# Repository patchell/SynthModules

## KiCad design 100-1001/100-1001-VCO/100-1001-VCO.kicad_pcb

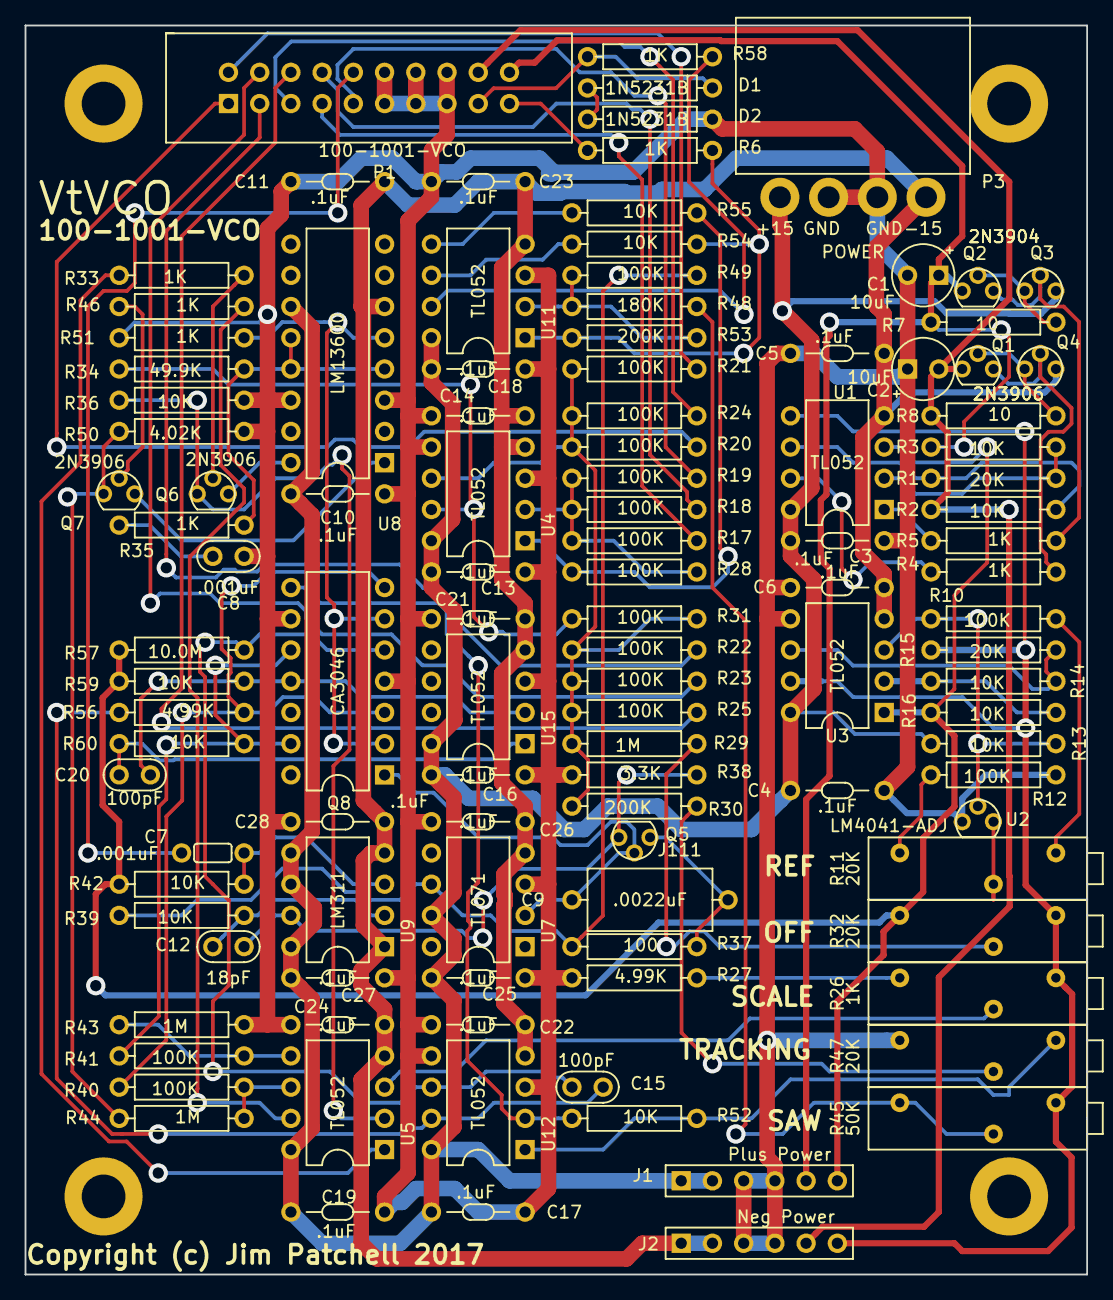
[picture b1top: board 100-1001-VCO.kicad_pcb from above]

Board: 2 copper layers, 86.4 x 101.6 mm, 116 parts (0 on the bottom side), 75 nets.

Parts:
C1, C2: 10uF; Cap-Pol-Rad-0.2_0.1
C3, C4, C5, C6, C10, C11, C13, C14, C16, C17, C18, C19, C21, C22, C23, C24, C25, C26, C27, C28: .1uF; CAP-Bypass-0.3
C7: .001uF; CAP-GREENIE-0.2
C8: .001uF; CAP-0.1
C9: .0022uF; CAP-AXIAL-0.5x0.2
C12: 18pF; CAP-0.1
C15, C20: 100pF; CAP-0.1
D1, D2: 1N5231B; DIODE0.4
J1: Plus Power; Header-6p-Stackable
J2: Neg Power; Header-6p-Stackable
P1: 100-1001-VCO; IDC10x2_Vert
P3: POWER; MTA0156x4_RA
P4, P5, P6, P7: PAD; MountingHole_140
Q1, Q4, Q6, Q7: 2N3906; TO92
Q2, Q3: 2N3904; TO92
Q5: J111; TO92
Q8: CA3046; DIP-14.3
R1, R15: 20K; AXIAL0.4
R2, R3, R13, R14, R16, R36, R39, R42, R52, R54, R55, R59, R60: 10K; AXIAL0.4
R4, R5, R6, R33, R35, R46, R51, R58: 1K; AXIAL0.4
R7, R8: 10; AXIAL0.4
R10, R12, R17, R18, R19, R20, R21, R22, R23, R24, R25, R28, R31, R40, R41, R49: 100K; AXIAL0.4
R11, R32, R47: 20K; Trimpot-3006
R26: 1K; Trimpot-3006
R27, R56: 4.99K; AXIAL0.4
R29, R43, R44: 1M; AXIAL0.4
R30, R53: 200K; AXIAL0.4
R34: 49.9K; AXIAL0.4
R37: 100; AXIAL0.4
R38: 3.3K; AXIAL0.4
R45: 50K; Trimpot-3006
R48: 180K; AXIAL0.4
R50: 4.02K; AXIAL0.4
R57: 10.0M; AXIAL0.4
U1, U3, U4, U5, U11, U12, U15: TL052; DIP8.3
U2: LM4041-ADJ; TO92
U7: TL071; DIP8.3
U8: LM13600; DIP-16.3
U9: LM311; DIP8.3

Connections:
+10: C1.1, J1.5, P1.20, Q2.1, R3.1, R7.1
+15V0: C3.1, C4.1, C10.1, C13.1, C16.1, C17.1, C18.1, C19.1, C25.1, C27.1, J1.1, J1.2, P3.1, Q3.3, R13.1, U1.8, U3.8, U4.8, U5.8, U7.7, U8.11, U9.5, U9.6, U9.8, U11.8, U12.8, U15.8
-10: C2.2, J2.5, P1.18, Q1.1, R2.1, R8.2
-15V0: C5.1, C6.1, C11.1, C14.1, C21.1, C22.1, C23.1, C24.1, C26.1, C28.1, J2.1, J2.2, P3.4, Q4.3, U1.4, U3.4, U4.4, U5.4, U7.4, U8.6, U9.1, U9.4, U11.4, U12.4, U15.4
/+5V: J1.6, R16.1, R32.3, R42.2, R57.1, R59.1, U1.3, U3.1
/-5V: J2.6, R15.1, R26.1, R32.1, R45.1, U1.5, U3.7
/VCO1/PULSE: D1.1, P1.17, R58.2
/VCO1/PWM1: P1.7, R17.1
/VCO1/PWM2: P1.8, R18.1
/VCO1/PWM3: P1.9, R19.1
/VCO1/RAMP: R6.1, R53.2, R54.1, U11.1
/VCO1/SYNC: C7.1, P1.10
/VCO1/VCO1: P1.1, R20.1
/VCO1/VCO2: P1.2, R21.1
/VCO1/VCO3: P1.3, R22.1
/VCO1/VCO4: P1.4, R23.1
/VCO1/VCO5: P1.5, R24.1
/VCO1/VCO6: P1.6, R25.1
GND: C1.2, C2.1, C3.2, C4.2, C5.2, C6.2, C8.2, C10.2, C11.2, C13.2, C14.2, C16.2, C17.2, C18.2, C19.2, C21.2, C22.2, C23.2, C24.2, C25.2, C26.2, C27.2, C28.2, D2.1, J1.3, J1.4, J2.3, J2.4, P1.11, P1.12, P1.13, P1.14, P1.15, P1.16, P3.2, P3.3, Q8.4, Q8.9, R12.2, R27.2, R36.2, R38.2, R43.2, R47.3, R50.2, R51.2, U2.1, U3.5, U4.3, U4.5, U7.3, U8.3, U8.14, U11.3, U12.3, U12.5, U15.3
unnamed: C7.2, R42.1, U9.3
unnamed: C8.1, R35.2
unnamed: C9.1, Q5.2, Q8.1, U7.2
unnamed: C9.2, Q5.1, R37.1
unnamed: C12.1, R39.2, U9.2
unnamed: C12.2, Q5.3, R38.1, U9.7
unnamed: C15.1, Q8.5, R57.2, U12.6
unnamed: C15.2, R56.2, U12.7
unnamed: C20.1, Q8.11, R59.2, U15.2
unnamed: C20.2, R60.2, U15.1
unnamed: D1.2, D2.2
unnamed: P1.19, R6.2
unnamed: Q1.2, Q4.1, R8.1
unnamed: Q1.3, Q4.2, R4.1
unnamed: Q2.2, Q3.1, R7.2
unnamed: Q2.3, Q3.2, R5.1
unnamed: Q6.1, R36.1, U5.2
unnamed: Q6.2, R33.2
unnamed: Q6.3, U8.16
unnamed: Q7.1, R44.2, R50.1
unnamed: Q7.2, R46.2
unnamed: Q7.3, U8.1
unnamed: Q8.2, Q8.6, R51.1, U8.5
unnamed: Q8.3, Q8.7, R40.1, R56.1
unnamed: Q8.8, R52.2, U12.2
unnamed: Q8.10, Q8.13, R41.1, R60.1
unnamed: R1.1, R2.2, U1.6
unnamed: R1.2, R3.2, U1.2
unnamed: R4.2, U1.7
unnamed: R5.2, U1.1
unnamed: R10.1, R13.2, U2.2, U3.3
unnamed: R10.2, R11.1
unnamed: R11.2, U2.3
unnamed: R11.3, R12.1
unnamed: R14.1, R16.2, U3.2
unnamed: R14.2, R15.2, U3.6
unnamed: R17.2, R18.2, R19.2, R28.1, U4.2
unnamed: R20.2, R21.2, R22.2, R23.2, R24.2, R25.2, R29.1, R30.1, R31.1, U4.6
unnamed: R26.2, U5.3
unnamed: R26.3, R27.1
unnamed: R28.2, R55.1, U4.1
unnamed: R29.2, R32.2
unnamed: R30.2, R47.2
unnamed: R31.2, R34.1, U4.7
unnamed: R33.1, U5.1
unnamed: R34.2, R35.1, U8.4, U8.12, U8.13
unnamed: R37.2, R39.1, R49.1, U7.6
unnamed: R40.2, R44.1, U5.6
unnamed: R41.2, R43.1, U5.5
unnamed: R45.2, R45.3, R48.1
unnamed: R46.1, U5.7
unnamed: R47.1, R52.1, U12.1
unnamed: R48.2, R49.2, R53.1, U11.2
unnamed: R54.2, U11.6
unnamed: R55.2, U11.5
unnamed: R58.1, U11.7

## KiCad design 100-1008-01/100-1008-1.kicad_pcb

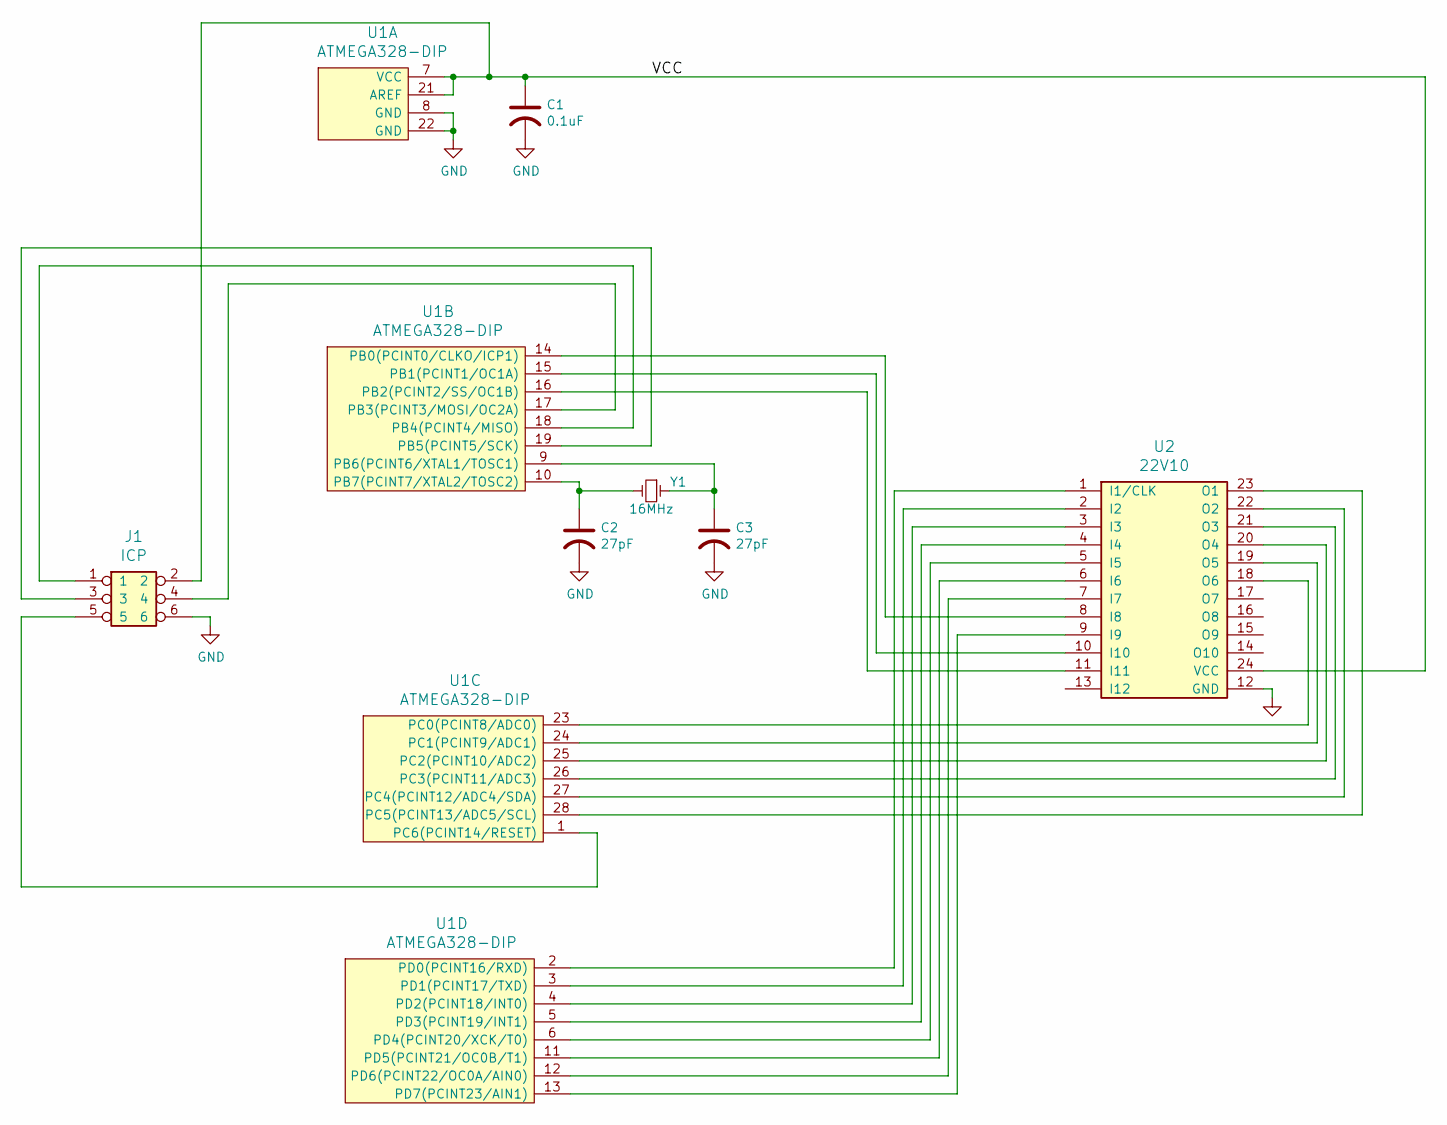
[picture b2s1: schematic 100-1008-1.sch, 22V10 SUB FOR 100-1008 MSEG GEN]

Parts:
C1: 0.1uF; CAP-Bypass-0.3
C2, C3: 27pF; CAP-0.1
J1: ICP; IDC3X2
U1: ATMEGA328-DIP; DIP28.3
U2: 22V10; DIP24.3
Y1: 16MHz; XTAL

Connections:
/VCC: C1.1, J1.2, U1.7 (VCC), U1.21 (AREF), U2.24 (VCC)
GND: C1.2, C2.2, C3.2, J1.6, U1.8 (GND), U1.22 (GND), U2.12 (GND)
unnamed: C2.1, U1.10 (PB7(PCINT7/XTAL2/TOSC2)), Y1.2
unnamed: C3.1, U1.9 (PB6(PCINT6/XTAL1/TOSC1)), Y1.1
unnamed: J1.1, U1.18 (PB4(PCINT4/MISO))
unnamed: J1.3, U1.19 (PB5(PCINT5/SCK))
unnamed: J1.4, U1.17 (PB3(PCINT3/MOSI/OC2A))
unnamed: J1.5, U1.1 (PC6(PCINT14/RESET))
unnamed: U1.2 (PD0(PCINT16/RXD)), U2.1 (I1/CLK)
unnamed: U1.3 (PD1(PCINT17/TXD)), U2.2 (I2)
unnamed: U1.4 (PD2(PCINT18/INT0)), U2.3 (I3)
unnamed: U1.5 (PD3(PCINT19/INT1)), U2.4 (I4)
unnamed: U1.6 (PD4(PCINT20/XCK/T0)), U2.5 (I5)
unnamed: U1.11 (PD5(PCINT21/OC0B/T1)), U2.6 (I6)
unnamed: U1.12 (PD6(PCINT22/OC0A/AIN0)), U2.7 (I7)
unnamed: U1.13 (PD7(PCINT23/AIN1)), U2.9 (I9)
unnamed: U1.14 (PB0(PCINT0/CLKO/ICP1)), U2.8 (I8)
unnamed: U1.15 (PB1(PCINT1/OC1A)), U2.10 (I10)
unnamed: U1.16 (PB2(PCINT2/SS/OC1B)), U2.11 (I11)
unnamed: U1.23 (PC0(PCINT8/ADC0)), U2.18 (O6)
unnamed: U1.24 (PC1(PCINT9/ADC1)), U2.19 (O5)
unnamed: U1.25 (PC2(PCINT10/ADC2)), U2.20 (O4)
unnamed: U1.26 (PC3(PCINT11/ADC3)), U2.21 (O3)
unnamed: U1.27 (PC4(PCINT12/ADC4/SDA)), U2.22 (O2)
unnamed: U1.28 (PC5(PCINT13/ADC5/SCL)), U2.23 (O1)

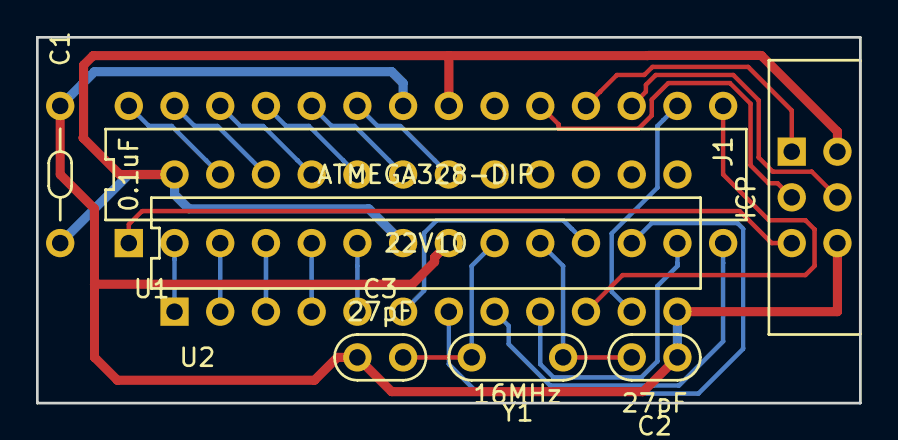
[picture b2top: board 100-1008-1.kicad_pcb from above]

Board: 2 copper layers, 45.7 x 20.3 mm, 7 parts (0 on the bottom side), 25 nets.

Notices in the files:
100-1001/100-1001-VCO/100-1001-VCO.kicad_pcb:
Copyright (c) Jim Patchell 2017
100-1059D/100-1059D_Cheezy.kicad_pcb:
COPYRIGHT (C) 2018
300-1002/300-1002.kicad_pcb:
Copyright (c) 2019
